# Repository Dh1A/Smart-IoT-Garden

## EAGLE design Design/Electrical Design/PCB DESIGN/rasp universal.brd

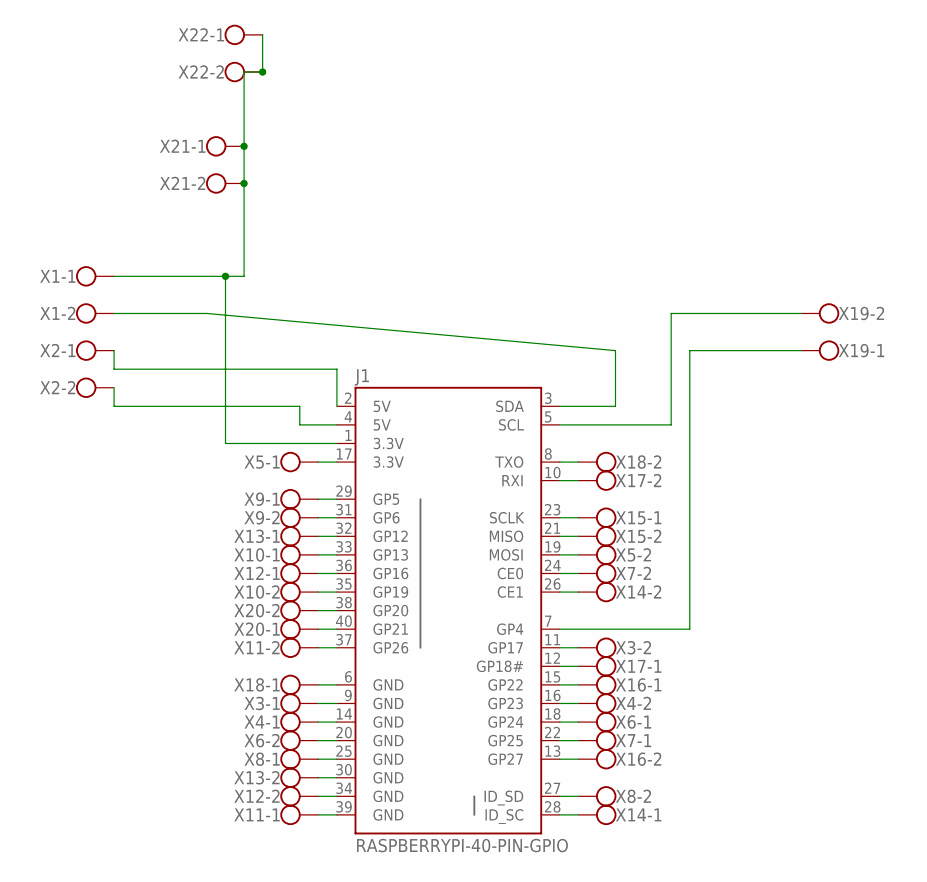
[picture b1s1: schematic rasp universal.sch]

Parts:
J1: RASPBERRYPI-40-PIN-GPIO; 2X20-SHROUDED
X1, X2, X3, X4, X5, X6, X7, X8, X9, X10, X11, X12, X13, X14, X15, X16, X17, X18, X19, X20, X21, X22: W237-102

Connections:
unnamed: J1.1 (3.3V), X1.1, X21.1, X21.2, X22.1, X22.2
unnamed: J1.3 (SDA), X1.2
unnamed: J1.2 (5V), X2.1
unnamed: J1.4 (5V), X2.2
unnamed: J1.5 (SCL), X19.2
unnamed: J1.7 (GP4), X19.1
unnamed: J1.6 (GND), X18.1
unnamed: J1.8 (TXO), X18.2
unnamed: J1.9 (GND), X3.1
unnamed: J1.11 (GP17), X3.2
unnamed: J1.12 (GP18#), X17.1
unnamed: J1.10 (RXI), X17.2
unnamed: J1.15 (GP22), X16.1
unnamed: J1.13 (GP27), X16.2
unnamed: J1.14 (GND), X4.1
unnamed: J1.16 (GP23), X4.2
unnamed: J1.17 (3.3V), X5.1
unnamed: J1.19 (MOSI), X5.2
unnamed: J1.20 (GND), X6.2
unnamed: J1.18 (GP24), X6.1
unnamed: J1.23 (SCLK), X15.1
unnamed: J1.21 (MISO), X15.2
unnamed: J1.24 (CE0), X7.2
unnamed: J1.22 (GP25), X7.1
unnamed: J1.27 (ID_SD), X8.2
unnamed: J1.25 (GND), X8.1
unnamed: J1.28 (ID_SC), X14.1
unnamed: J1.26 (CE1), X14.2
unnamed: J1.29 (GP5), X9.1
unnamed: J1.31 (GP6), X9.2
unnamed: J1.32 (GP12), X13.1
unnamed: J1.30 (GND), X13.2
unnamed: J1.35 (GP19), X10.2
unnamed: J1.33 (GP13), X10.1
unnamed: J1.36 (GP16), X12.1
unnamed: J1.34 (GND), X12.2
unnamed: J1.39 (GND), X11.1
unnamed: J1.37 (GP26), X11.2
unnamed: J1.40 (GP21), X20.1
unnamed: J1.38 (GP20), X20.2

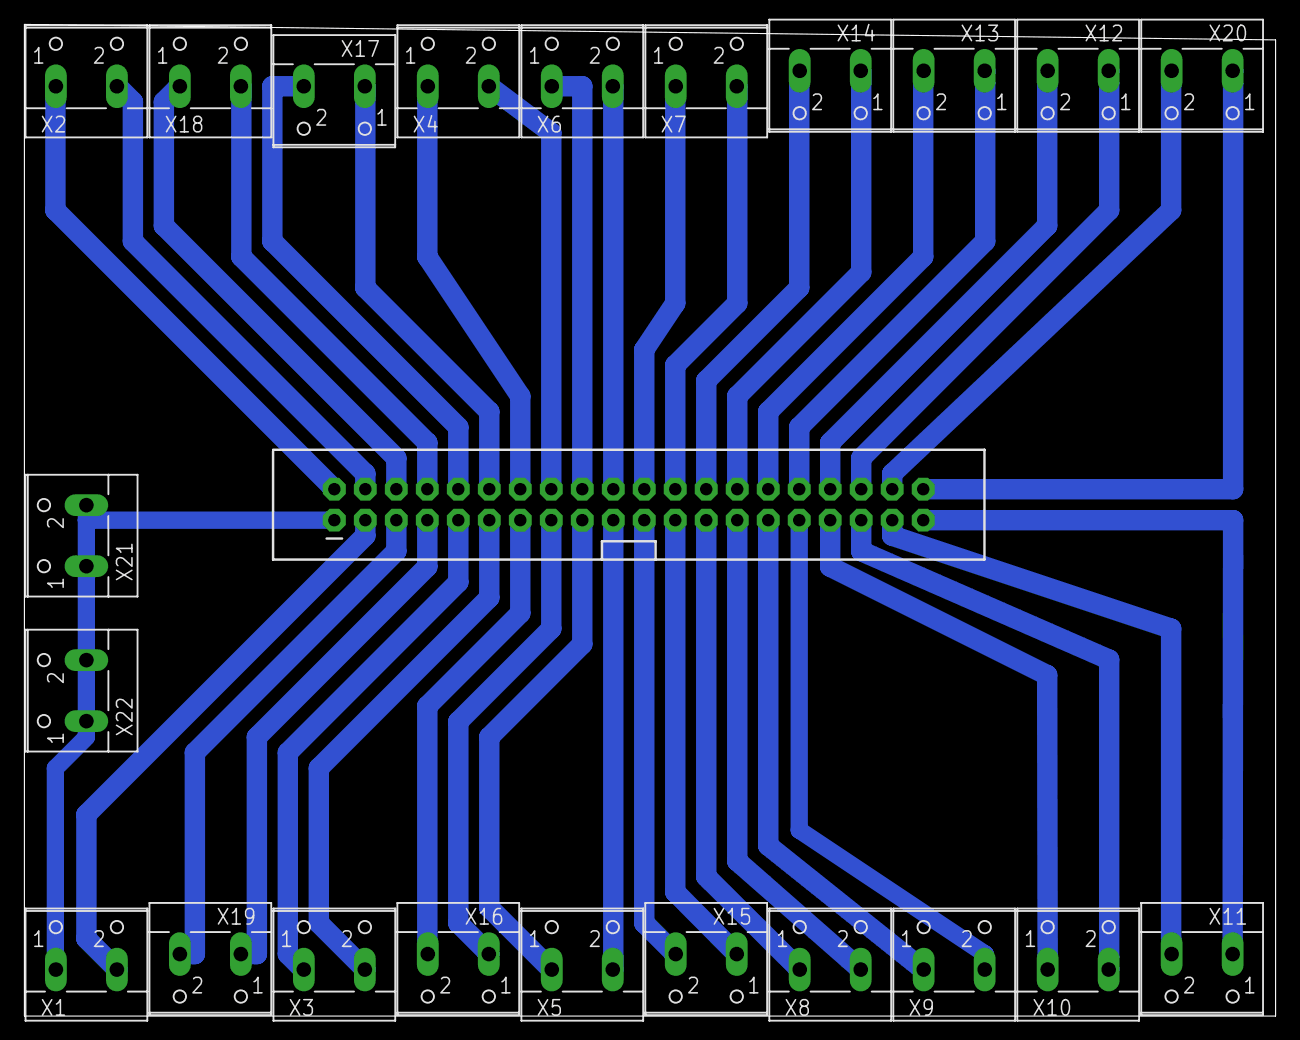
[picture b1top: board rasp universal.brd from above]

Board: 2 copper layers, 102.5 x 81.3 mm, 23 parts (0 on the bottom side), 40 nets.

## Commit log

2017-11-13 :confetti_ball: Added .gitattributes & .gitignore files
2017-11-13 Smart IoT Garden
    Smart IoT Garden

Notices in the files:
parts and their libraries:
SparkFun-Boards: Licensing: Creative Commons ShareAlike 4.0 International - https://creativecommons.org/licenses/by-sa/4.0
